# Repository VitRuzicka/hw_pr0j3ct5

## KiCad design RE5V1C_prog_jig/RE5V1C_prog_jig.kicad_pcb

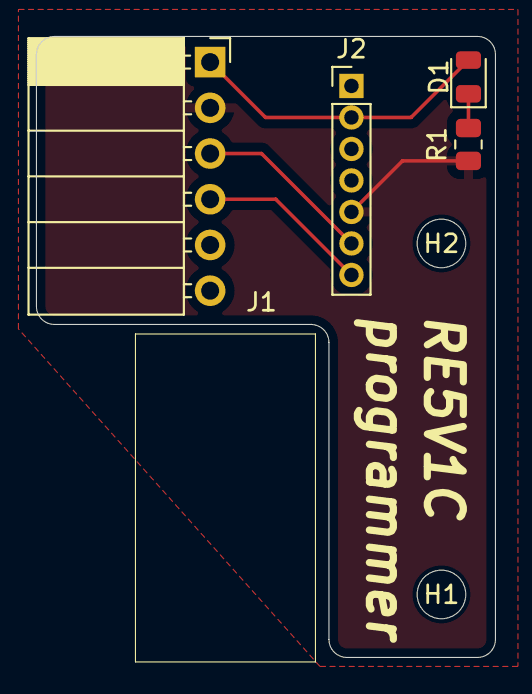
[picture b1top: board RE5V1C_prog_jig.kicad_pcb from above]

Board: 2 copper layers, 25.5 x 34.5 mm, 6 parts (0 on the bottom side), 5 nets.

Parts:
D1: LED; D_0805_2012Metric
H1, H2: MountingHole; MountingHole_2.7mm_M2.5
J1: LASKAKIT_PROG; PinSocket_1x06_P2.54mm_Horizontal
J2: SONOFF RE5V1C; PinHeader_1x07_P2.00mm_Vertical
R1: 1k; R_0805_2012Metric

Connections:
/GND: J1.2, J2.5, R1.2
/RX: J1.4, J2.7
/TX: J1.3, J2.6
/VCC: D1.2 (A), J1.1, J2.2
unnamed: D1.1 (K), R1.1

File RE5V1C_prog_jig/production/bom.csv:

Designator,Footprint,Quantity,Value,LCSC Part #
D1,0805,1,LED,
J1,PinSocket_1x06_P2.54mm_Horizontal,1,LASKAKIT_PROG,
J2,PinHeader_1x07_P2.00mm_Vertical,1,SONOFF RE5V1C,
R1,0805,1,1k,

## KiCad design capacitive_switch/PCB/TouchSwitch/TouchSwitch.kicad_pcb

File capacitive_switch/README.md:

<h1>This is capacitive switch</h1>
<p>What can it do, I hear you ask. Well, just look:</p>

<p>The code is poorly written in ARDUINO ide, but who cares, right?</p>
<p>I would love to see someone make drop-in replacement for sonoff touch switch, but Im too lazy to do that, maybe later</p>
<p>For the function: it uses two ttp223 controllers to detect change in capacitance on two copper fills places on one side and therefore is able to detect basic gestures. I've only used it to detect if Im sliding the finger up to bottom(to turn off the output) or from bottom to up. It was also the test of ch32v003 and the <a href="https://github.com/cnlohr/ch32v003fun">corresponding repository</a> from cnlohr, which is awesome.</p>

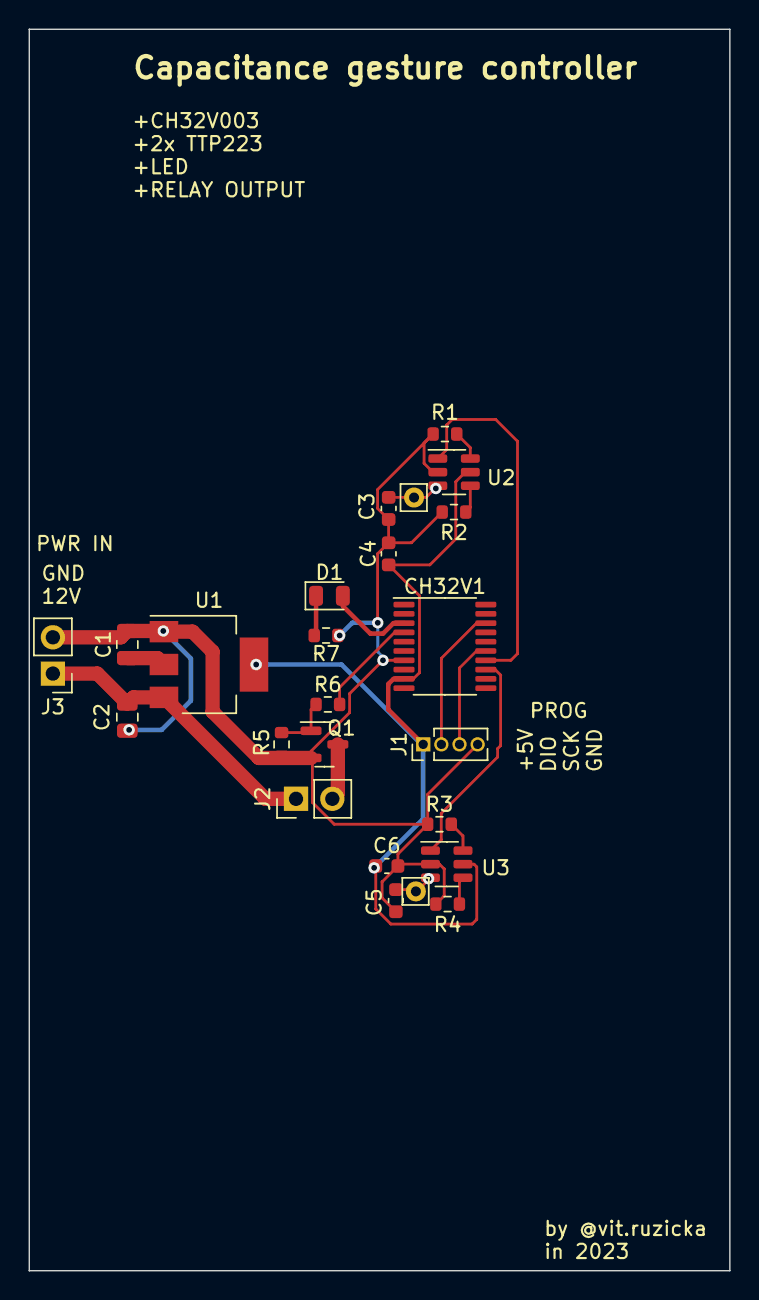
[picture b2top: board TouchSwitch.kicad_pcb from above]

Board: 2 copper layers, 49.0 x 86.9 mm, 22 parts (0 on the bottom side), 18 nets.

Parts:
C1, C2: 1uF; C_0805_2012Metric
C3, C5: C; C_0603_1608Metric
C4, C6: 100n; C_0603_1608Metric
CH32V1: CH32V003_TSSOP20; TSSOP-20_4.4x6.5mm_P0.65mm
D1: LED; D_0805_2012Metric
J1: Conn_01x04; PinHeader_1x04_P1.27mm_Vertical
J2, J3: Conn_01x02; PinHeader_1x02_P2.54mm_Vertical
Q1: BC817; SOT-23
R1, R2, R3, R4, R5, R6, R7: R; R_0603_1608Metric
U1: AMS1117-5.0; SOT-223-3_TabPin2
U2, U3: TTP223; SOT-23-6

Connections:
+5V: C1.1, C4.1, C6.1, CH32V1.9 (VDD), J1.1, U1.2 (VO), U2.5 (VCC), U3.5 (VCC)
+12V: C2.1, J2.1, J3.1, U1.3 (VI)
GND: C1.2, C2.2, C3.2, C4.2, C5.2, C6.2, CH32V1.7 (VSS), J1.4, J3.2, Q1.2 (E), R1.2, R2.2, R3.2, R4.2, R5.2, R7.2, U1.1 (GND), U2.2 (GND), U3.2 (GND)
unnamed: CH32V1.13 (PC3), U3.1 (OUT)
unnamed: CH32V1.14 (PC4), U2.1 (OUT)
unnamed: CH32V1.15 (PC5), J1.3
unnamed: CH32V1.18 (PD1/SCL0), J1.2
unnamed: CH32V1.3 (PD6), D1.2 (A)
unnamed: CH32V1.4 (PD7), R6.1
unnamed: D1.1 (K), R7.1
unnamed: J2.2, Q1.3 (C)
unnamed: Q1.1 (B), R5.1, R6.2
unnamed: R1.1, U2.6 (LATCH)
unnamed: R2.1, U2.4 (POL)
unnamed: R3.1, U3.6 (LATCH)
unnamed: R4.1, U3.4 (POL)
TOUCH1: C3.1, U2.3 (TOUCH)
TOUCH2: C5.1, U3.3 (TOUCH)

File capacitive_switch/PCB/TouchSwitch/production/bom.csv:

Designator,Footprint,Quantity,Value,LCSC Part #
"C1, C2",0805,2,1uF,
"C3, C5",0603,2,C,
"C4, C6",0603,2,100n,
CH32V1,TSSOP-20_4.4x6.5mm_P0.65mm,1,CH32V003_TSSOP20,
D1,0805,1,LED,
J1,PinHeader_1x04_P1.27mm_Vertical,1,Conn_01x04,
"J2, J3",PinHeader_1x02_P2.54mm_Vertical,2,Conn_01x02,
Q1,SOT-23,1,BC817,
"R1, R2, R3, R4, R5, R6, R7",0603,7,R,
U1,SOT-223-3_TabPin2,1,AMS1117-5.0,
"U2, U3",SOT-23-6,2,TTP223,

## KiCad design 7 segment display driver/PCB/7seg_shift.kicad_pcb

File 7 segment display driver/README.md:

# 7 segment driver
<br>
This project is simple driver for two displays of this type: 
<a href="https://www.tme.eu/cz/details/opd-s15013ly-bw/7-segment-led-displays/opto-plus-led/">TME link</a><br>
Houses two displays per module (daisy-chainable). One shift 74HC595 per register and has PWM.<br>
The main reason, why this exists is that there was a sale on the modules so I got them super cheap and the amber color looked really nice, so I've decided to build a <b>CLOCK</b>.<br>Features:<br><il>
<li>Easily expandable</li>
<li>PWM dimming
<li>ready for wemos backpack
<li>cool color
</il>

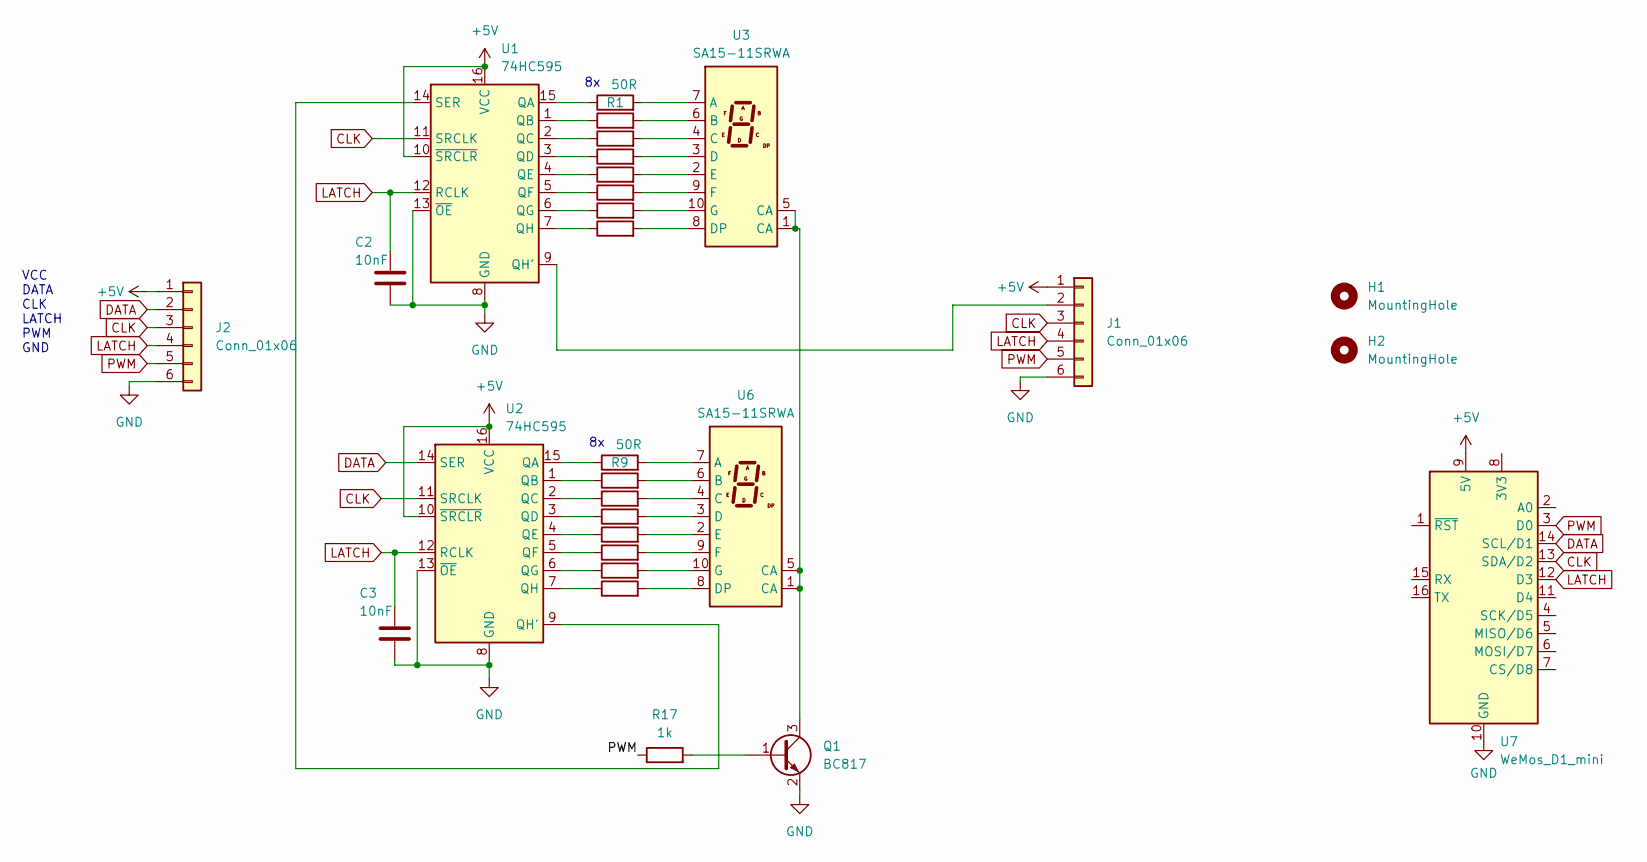
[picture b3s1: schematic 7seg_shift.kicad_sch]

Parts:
C2, C3: 10nF; C_0805_2012Metric
H1, H2: MountingHole; MountingHole_2.2mm_M2
J1: Conn_01x06; PinHeader_1x06_P2.54mm_Horizontal
J2: Conn_01x06; PinSocket_1x06_P2.54mm_Horizontal
Q1: BC817; SOT-23
R1, R9: 50R; R_0402_1005Metric_Pad0.72x0.64mm_HandSolder
R2, R3, R4, R5, R6, R7, R8, R10, R11, R12, R13, R14, R15, R16: 100R; R_0402_1005Metric_Pad0.72x0.64mm_HandSolder
R17: 1k; R_0805_2012Metric_Pad1.20x1.40mm_HandSolder
U1, U2: 74HC595; SOIC-16_3.9x9.9mm_P1.27mm
U3, U6: SA15-11SRWA; SA15-11xxx
U7: WeMos_D1_mini; WEMOS_D1_mini_light

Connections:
+5V: J1.1, J2.1, U1.10 (~SRCLR), U1.16 (VCC), U2.10 (~SRCLR), U2.16 (VCC), U7.9 (5V)
CLK: J1.3, J2.3, U1.11 (SRCLK), U2.11 (SRCLK), U7.13 (SDA/D2)
DATA: J2.2, U2.14 (SER), U7.14 (SCL/D1)
GND: C2.2, C3.2, J1.6, J2.6, Q1.2 (E), U1.8 (GND), U1.13 (~OE), U2.8 (GND), U2.13 (~OE), U7.10 (GND)
LATCH: C2.1, C3.1, J1.4, J2.4, U1.12 (RCLK), U2.12 (RCLK), U7.12 (D3)
unnamed: J1.2, U1.9 (QH')
unnamed: Q1.1 (B), R17.2
unnamed: Q1.3 (C), U3.1 (CA), U3.5 (CA), U6.1 (CA), U6.5 (CA)
unnamed: R1.1, U1.15 (QA)
unnamed: R2.1, U1.1 (QB)
unnamed: R3.1, U1.2 (QC)
unnamed: R4.1, U1.3 (QD)
unnamed: R5.1, U1.4 (QE)
unnamed: R6.1, U1.5 (QF)
unnamed: R7.1, U1.6 (QG)
unnamed: R8.1, U1.7 (QH)
unnamed: U1.14 (SER), U2.9 (QH')
unnamed: R9.1, U2.15 (QA)
unnamed: R10.1, U2.1 (QB)
unnamed: R11.1, U2.2 (QC)
unnamed: R12.1, U2.3 (QD)
unnamed: R13.1, U2.4 (QE)
unnamed: R14.1, U2.5 (QF)
unnamed: R15.1, U2.6 (QG)
unnamed: R16.1, U2.7 (QH)
unnamed: R1.2, U3.7 (A)
unnamed: R2.2, U3.6 (B)
unnamed: R3.2, U3.4 (C)
unnamed: R4.2, U3.3 (D)
unnamed: R8.2, U3.8 (DP)
unnamed: R5.2, U3.2 (E)
unnamed: R6.2, U3.9 (F)
unnamed: R7.2, U3.10 (G)
unnamed: R9.2, U6.7 (A)
unnamed: R10.2, U6.6 (B)
unnamed: R11.2, U6.4 (C)
unnamed: R12.2, U6.3 (D)
unnamed: R16.2, U6.8 (DP)
unnamed: R13.2, U6.2 (E)
unnamed: R14.2, U6.9 (F)
unnamed: R15.2, U6.10 (G)
PWM: J1.5, J2.5, R17.1, U7.3 (D0)

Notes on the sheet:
VCC DATA CLK LATCH PWM GND

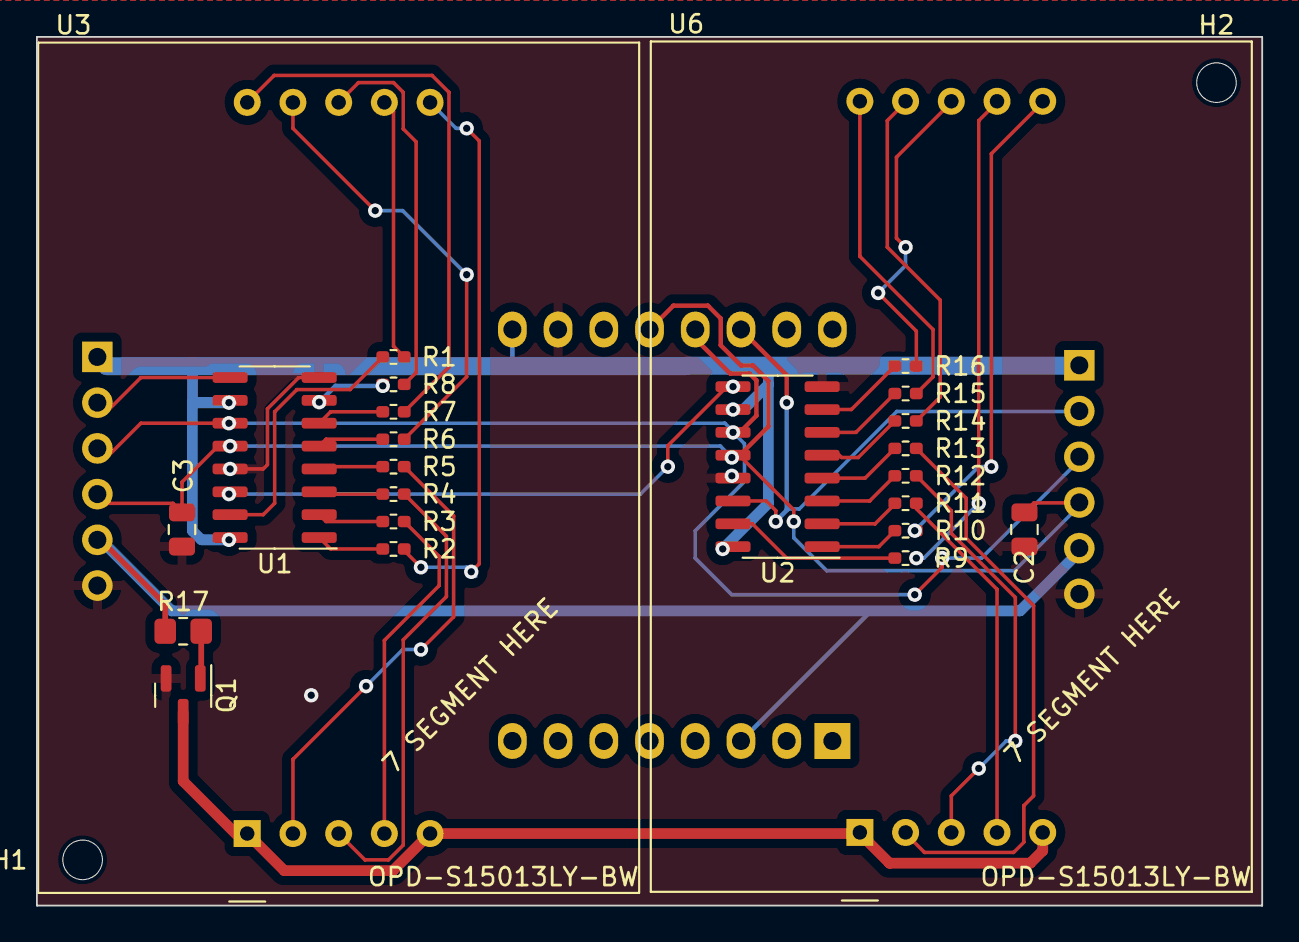
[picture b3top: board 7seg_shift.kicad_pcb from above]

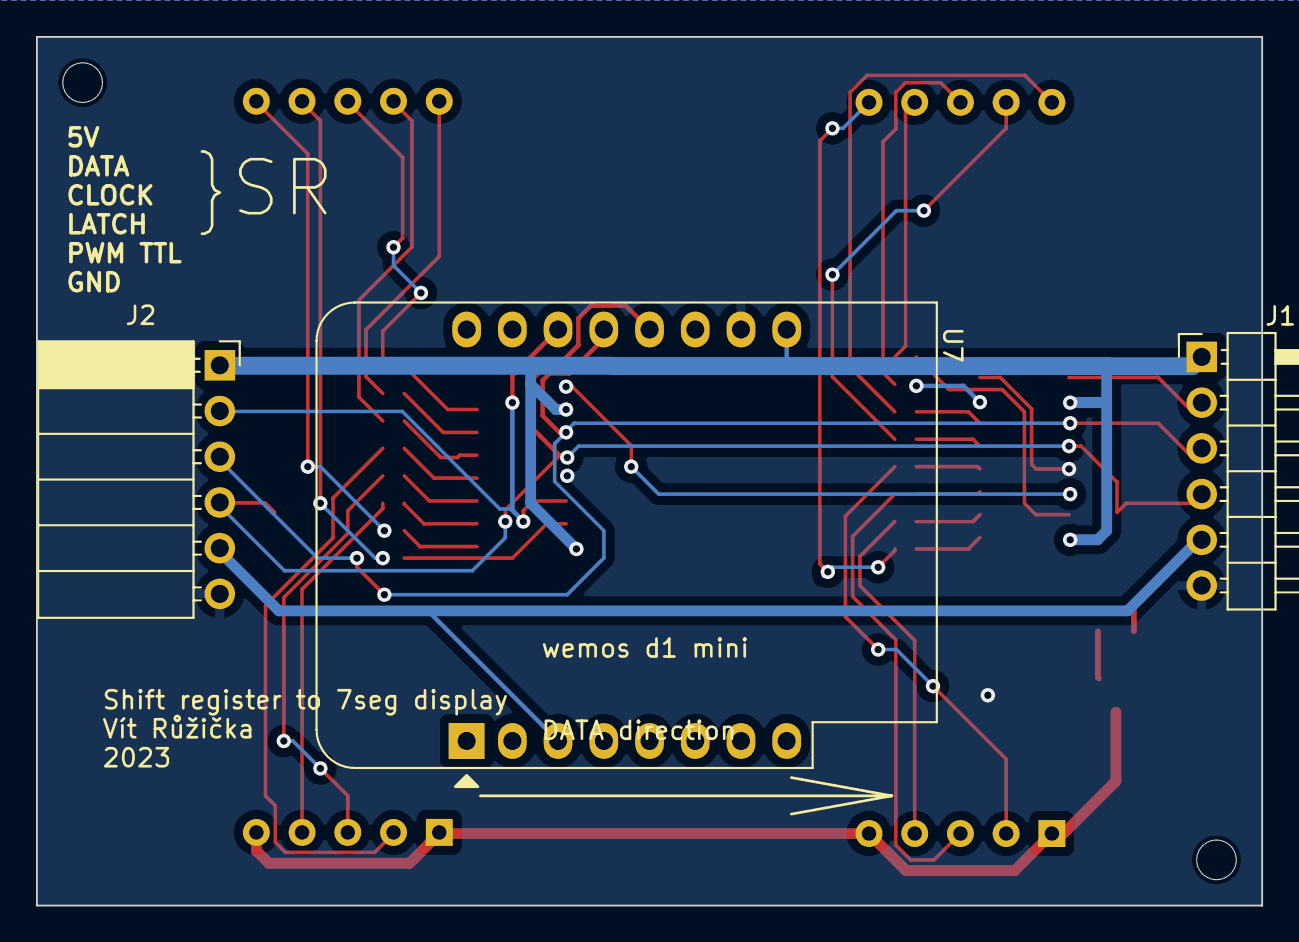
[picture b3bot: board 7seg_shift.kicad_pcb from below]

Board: 2 copper layers, 68.1 x 48.3 mm, 29 parts (3 on the bottom side), 42 nets.

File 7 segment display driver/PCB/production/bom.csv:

Designator,Footprint,Quantity,Value,LCSC Part #
"C2, C3",0805,2,10nF,
"H1, H2",MountingHole_2.2mm_M2,2,MountingHole,
J1,PinHeader_1x06_P2.54mm_Horizontal,1,Conn_01x06,
J2,PinSocket_1x06_P2.54mm_Horizontal,1,Conn_01x06,
Q1,SOT-23,1,BC817,
"R1, R9",0402,2,50R,
"R10, R11, R12, R13, R14, R15, R16, R2, R3, R4, R5, R6, R7, R8",0402,14,100R,
R17,0805,1,1k,
"U1, U2",SOIC-16_3.9x9.9mm_P1.27mm,2,74HC595,
"U3, U6",SA15-11xxx,2,SA15-11SRWA,
U7,WEMOS_D1_mini_light,1,WeMos_D1_mini,

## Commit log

2025-10-16 added readme and vindiktrig
2025-10-16 added wifi manager
2025-11-13 added sonoff programmer:
